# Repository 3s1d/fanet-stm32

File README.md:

# FANET
Flying Ad-hoc Network 

# IDE
Use SW4SRTM32

# Protocol
[Brief specification](https://github.com/3s1d/fanet-stm32/blob/master/Src/fanet/radio/protocol.txt)

# Documentation
[Module (PDF)](https://github.com/3s1d/fanet-stm32/raw/master/fanet_module.pdf)

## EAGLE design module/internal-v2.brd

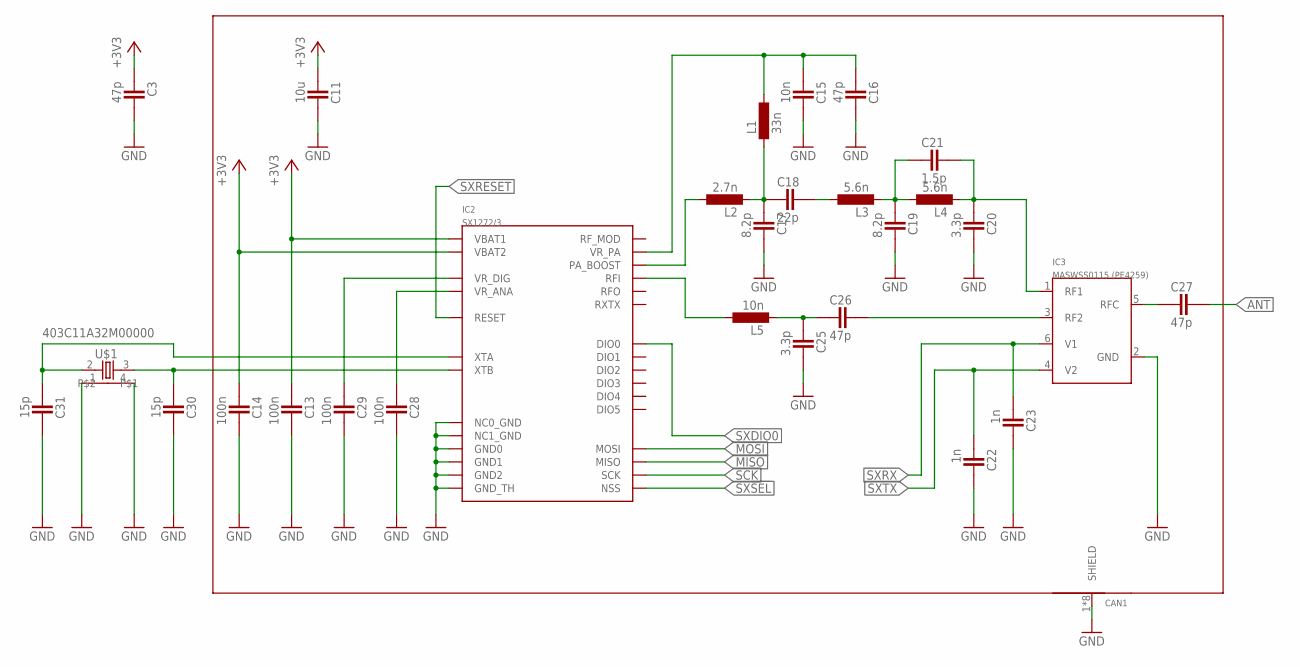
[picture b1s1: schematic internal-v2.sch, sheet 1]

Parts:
C3, C16, C26, C27: 47p; CAPC1005X60N
C11: 10u; CAPC2012X145AN
C13, C14, C28, C29: 100n; CAPC1005X60N
C15: 10n; CAPC1005X60N
C17, C19: 8.2p; CAPC1005X60N
C18: 22p; CAPC1005X60N
C20, C25: 3.3p; CAPC1005X60N
C21: 1.5p; CAPC1005X60N
C22, C23: 1n; CAPC1005X60N
C30, C31: 15p; CAPC1005X60N
CAN1: RF-SHIELD; RF-SHIELDING-13.66X12.70
IC2: SX1272/3; QFN28
IC3: MASWSS0115 (PE4259); SC-70
L1: 33n; INDC1005X60N
L2: 2.7n; INDC1005X60N
L3, L4: 5.6n; INDC1005X60N
L5: 10n; INDC1005X60N
U$1: 403C11A32M00000; MT

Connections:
+3V3: C3.1, C11.1, C13.1, C14.1, IC2.P$1 (VBAT1), IC2.P$15 (VBAT2); also elsewhere on the board
ANT: C27.2
GND: C3.2, C11.2, C13.2, C14.2, C15.2, C16.2, C17.2, C19.2, C20.2, C22.2, C23.2, C25.2, C28.2, C29.2, C30.2, C31.2, CAN1.1, CAN1.2, CAN1.3, CAN1.4, CAN1.5, CAN1.6, CAN1.7, CAN1.8, IC2.P$7 (NC0_GND), IC2.P$8 (NC1_GND), IC2.P$16 (GND0), IC2.P$22 (GND1), IC2.P$26 (GND2), IC2.P$29 (GND_TH), IC3.2 (GND), U$1.1, U$1.4; also elsewhere on the board
MISO: IC2.P$18 (MISO); also elsewhere on the board
MOSI: IC2.P$19 (MOSI); also elsewhere on the board
unnamed: IC2.P$27 (PA_BOOST), L2.2
unnamed: C17.1, C18.1, L1.1, L2.1
unnamed: C15.1, C16.1, IC2.P$28 (VR_PA), L1.2
unnamed: C18.2, L3.2
unnamed: C19.1, C21.1, L3.1, L4.2
unnamed: C27.1, IC3.5 (RFC)
unnamed: C20.1, C21.2, IC3.1 (RF1), L4.1
unnamed: IC2.P$25 (RFI), L5.2
unnamed: C25.1, C26.1, L5.1
unnamed: C26.2, IC3.3 (RF2)
unnamed: C28.1, IC2.P$2 (VR_ANA)
unnamed: C29.1, IC2.P$3 (VR_DIG)
unnamed: C30.1, IC2.P$5 (XTB), U$1.3 (2)
unnamed: C31.1, IC2.P$4 (XTA), U$1.2 (1)
SCK: IC2.P$17 (SCK); also elsewhere on the board
SX!SEL: IC2.P$20 (NSS); also elsewhere on the board
SXDIO0: IC2.P$9 (DIO0); also elsewhere on the board
SXRESET: IC2.P$6 (RESET); also elsewhere on the board
SXRX: C23.1, IC3.6 (V1); also elsewhere on the board
SXTX: C22.1, IC3.4 (V2); also elsewhere on the board

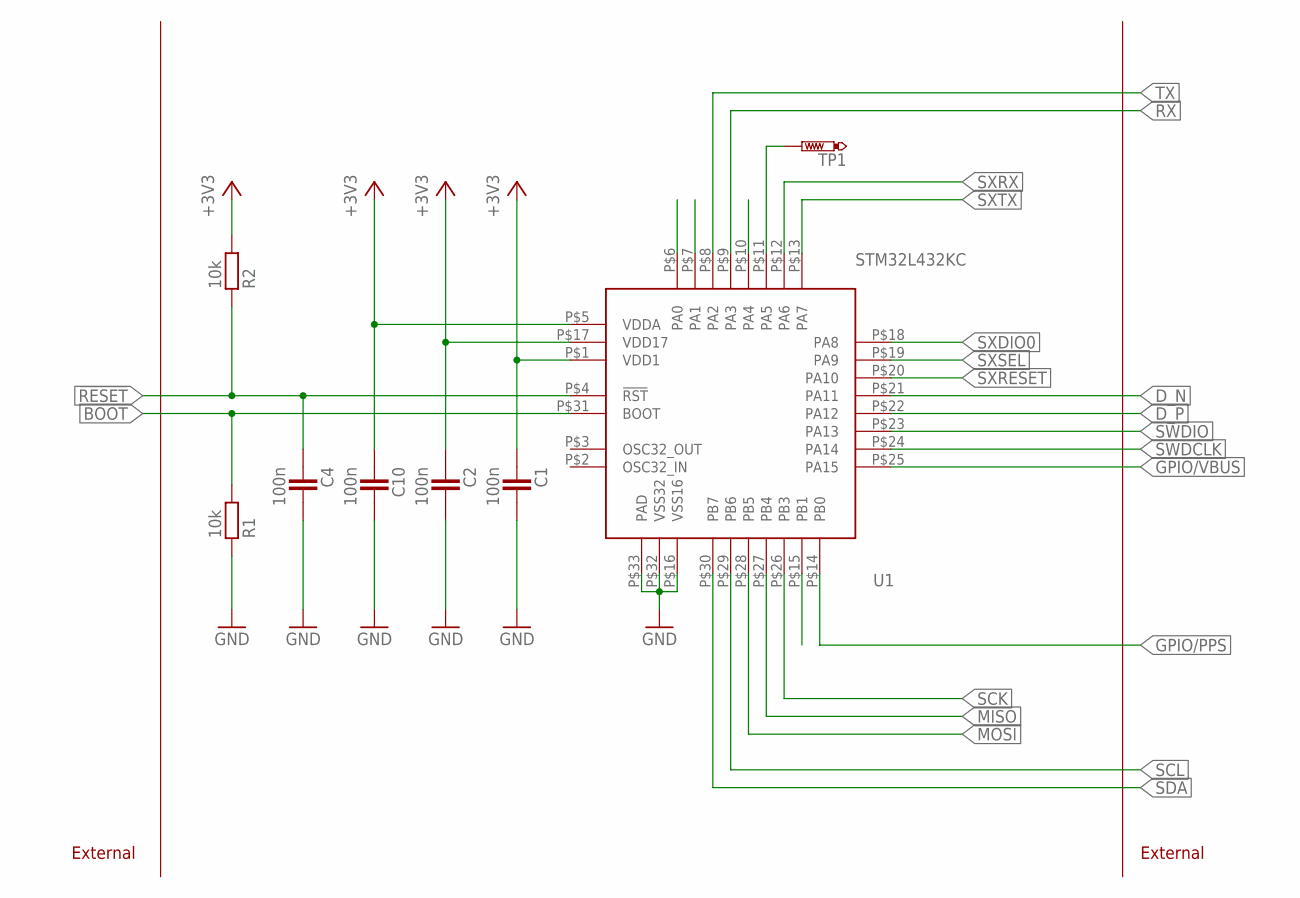
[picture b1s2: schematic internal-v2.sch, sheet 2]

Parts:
C1, C2, C4, C10: 100n; CAPC1005X60N
R1, R2: 10k; RESC1005X40AN
TP1: PTR1TP06R; TP06R
U1: STM32L432KC

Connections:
!RESET: C4.1, R2.1, U1.P$4 (!RST)
+3V3: C1.1, C2.1, C10.1, R2.2, U1.P$1 (VDD1), U1.P$5 (VDDA), U1.P$17 (VDD17); also elsewhere on the board
A0: U1.P$10 (PA4)
A1: TP1.TP, U1.P$11 (PA5)
A2: U1.P$6 (PA0)
A4: U1.P$15 (PB1)
BOOT: R1.2, U1.P$31 (BOOT)
D13: U1.P$7 (PA1)
D_N: U1.P$21 (PA11)
D_P: U1.P$22 (PA12)
GND: C1.2, C2.2, C4.2, C10.2, R1.1, U1.P$16 (VSS16), U1.P$32 (VSS32), U1.P$33 (PAD); also elsewhere on the board
GPIO/PPS: U1.P$14 (PB0)
GPIO/VBUS: U1.P$25 (PA15)
MISO: U1.P$27 (PB4); also elsewhere on the board
MOSI: U1.P$28 (PB5); also elsewhere on the board
RX: U1.P$9 (PA3)
SCK: U1.P$26 (PB3); also elsewhere on the board
SCL: U1.P$29 (PB6)
SDA: U1.P$30 (PB7)
SWDCLK: U1.P$24 (PA14)
SWDIO: U1.P$23 (PA13)
SX!SEL: U1.P$19 (PA9); also elsewhere on the board
SXDIO0: U1.P$18 (PA8); also elsewhere on the board
SXRESET: U1.P$20 (PA10); also elsewhere on the board
SXRX: U1.P$12 (PA6); also elsewhere on the board
SXTX: U1.P$13 (PA7); also elsewhere on the board
TX: U1.P$8 (PA2)

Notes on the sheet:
External

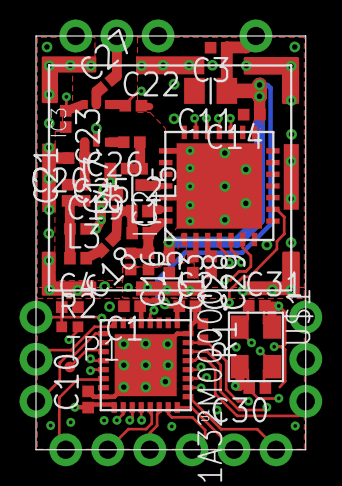
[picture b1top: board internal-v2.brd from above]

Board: 4 copper layers, 15.0 x 23.0 mm, 37 parts (0 on the bottom side), 27 nets.

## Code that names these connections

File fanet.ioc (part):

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Mcu.UserName=STM32L432KCUx
PA9.GPIOParameters=GPIO_Label
PA2.GPIO_Speed=GPIO_SPEED_FREQ_VERY_HIGH
PA3.GPIOParameters=GPIO_Speed
PB0.GPIO_Label=GPIO_PPS_EXTI0
PA6.GPIO_Label=SXRX
PB4\ (NJTRST).GPIO_Speed=GPIO_SPEED_FREQ_VERY_HIGH
PA3.GPIO_Speed=GPIO_SPEED_FREQ_VERY_HIGH
PA2.GPIOParameters=GPIO_Speed
RCC.SYSCLKSource=RCC_SYSCLKSOURCE_PLLCLK
PB3\ (JTDO-TRACESWO).Signal=SPI3_SCK
PB5.GPIOParameters=GPIO_Speed
PA14\ (JTCK-SWCLK).Signal=SYS_JTCK-SWCLK
PA8.GPIOParameters=GPIO_PuPd,GPIO_Label
RCC.HSE_VALUE=8000000
PB0.GPIOParameters=GPIO_PuPd,GPIO_Label
PB5.Mode=Full_Duplex_Master
PA10.GPIO_Label=SXRESET
PA8.Signal=GPXTI8
Mcu.Package=UFQFPN32
PA6.Signal=GPIO_Output
PA10.Signal=GPIO_Output
PA5.GPIOParameters=GPIO_Label
PB5.GPIO_Speed=GPIO_SPEED_FREQ_VERY_HIGH
PA13\ (JTMS-SWDIO).Signal=SYS_JTMS-SWDIO
PA3.Signal=LPUART1_RX
PA6.GPIOParameters=GPIO_Label
PA14\ (JTCK-SWCLK).Mode=Serial_Wire
PA9.GPIO_Label=SXSEL
PA3.Mode=Asynchronous
PB4\ (NJTRST).GPIOParameters=GPIO_Speed
PA8.GPIO_Label=SXDIO0_EXTI8
PA9.Signal=GPIO_Output
PA5.Signal=GPIO_Output
board=fanet
PB3\ (JTDO-TRACESWO).GPIOParameters=GPIO_Speed
PB3\ (JTDO-TRACESWO).Mode=Full_Duplex_Master
PA10.GPIOParameters=GPIO_Label
PB4\ (NJTRST).Mode=Full_Duplex_Master
Mcu.Name=STM32L432K(B-C)Ux
PA2.Signal=LPUART1_TX
PA13\ (JTMS-SWDIO).Mode=Serial_Wire
RCC.SYSCLKFreq_VALUE=18000000
PB5.Signal=SPI3_MOSI
PA7.GPIO_Label=SXTX
PA5.GPIO_Label=TP1
PA8.GPIO_PuPd=GPIO_PULLDOWN
PA2.Mode=Asynchronous
PB3\ (JTDO-TRACESWO).GPIO_Speed=GPIO_SPEED_FREQ_VERY_HIGH
PB0.Signal=GPXTI0
PA7.GPIOParameters=GPIO_Label
PB0.GPIO_PuPd=GPIO_PULLDOWN
PA7.Signal=GPIO_Output
PB4\ (NJTRST).Signal=SPI3_MISO

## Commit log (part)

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2017-05-21 sx1272 working
2017-05-22 fanet working w/o arduino
2017-05-22 readme added
2017-05-22 bumped start to 0x08010000
2017-05-23 cproject
2017-05-23 changed to IT transmitt
2017-05-23 fixed blocking uart
2017-05-24 cleanup
2017-06-05 proper debug scheme
2017-06-05 large packages (>32bytes payload) could potentially have blocked the hole network by blocking athe transmitter. fixed
2017-06-05 typos
2017-06-05 removed mac debugging
2017-08-16 protcol improved by absolute coordinates
2017-08-30 updated app to support new absolute coordinate system
2017-08-31 somem more FLARM relevant extentions
2017-09-03 FSK support added
2017-09-09 GFSK is working
2017-09-09 changed syncword. added airtime model
2017-09-11 address gets stored in flash
2017-09-12 revisited airtime duty cycle model
2017-09-15 sx_receive protected
2017-09-15 reorganized file structure
2017-09-17 bumped to 1.9.0 and removed unneeded buses like USB and I2C
2017-09-17 adjusted frq source to compensate thermal drift
2017-09-19 serial interface extend by fault hanlding
2017-09-19 typo
2017-09-19 minor rounding issue
2017-09-19 minor protocl adjustments
2017-09-28 protocol extension
2017-09-28 added modul eagle library
2017-10-11 pdf added
2017-10-11 extended README
2017-10-12 protocoll extended
2017-10-13 revised remote config
2017-10-14 remote configuration and signature intorduced
2017-10-15 signature corrected
2017-12-06 Manufacturer ID for SoftRF
2018-01-12 tweaked FSK freq. setting FLARM types during operation
2018-05-06 neg turnrate bugfix
2018-06-08 new type
2018-07-04 minor bugfixes
2018-09-29 FANET 1.1
    -code cleanup
    -ground tracking
    -improved landmark interface
2018-09-29 docu
2018-10-02 added geoid separation for FLARM altitudes
2018-10-19 new manucaturer id
2018-10-28 added manufacturer id
2018-11-15 Add Battery Voltage to Service (Type = 4) payload in Fanet protocol
2018-11-15 added softrf manufacturer
2018-11-15 added state of charge for base statinos
2019-06-10 protocol adjustments (landmarks becoming stable)
2019-06-12 wrong comment
2019-06-14 landmark scheme slightly reworked
2019-06-14 added dev flag
2019-06-15 compressed coordinates sample code
2019-06-15 extended landmark circle api
2019-06-15 enlarged radii for landmarks
2019-06-15 unified landmark data sequence
2019-06-21 3d landmarks altitude adjusted/expanded
2019-06-25 wind dependent landmarks
2019-06-26 landmark no wind option
2019-07-13 update remote config
2019-07-24 geo-based forwarding flag (can be ignored by any none-forwarding instances).
2019-07-30 Forwarding bugfix for ACK'ed frames...
2019-08-16 removed unstable us delay
2019-08-20 bootloader updater added
2019-08-20 removed unused code
2019-08-21 landmarks are stabile
2019-08-21 Fanet 1.2 (landmarks)
2019-09-19 comments orrected
2019-10-18 protocol extentions -3d tracking now supports QNE -hardware info for statistics, network optimization (experimental)
2019-10-18 adapated serial interface docu. code still pending
2019-10-19 improved description
2019-10-29 HW info pull'able
2020-02-14 fanet protocol extension
2020-03-16 DF Manufacturer ID
    For DF FANET base and weather station
2020-03-16 added ogn reserved area
2020-03-20 more stabile serial interface
2020-03-21 serial dma circular buffer fix, casw schedluing
2020-05-20 type 1 optinal byes added
2020-05-20 ogn tracker manu id
2020-05-20 changed ogn ID
2020-05-25 -type 1 extrended to fit OGN, Naviter requirements -thermal defined stabile -hw info new defined. experimantal
2020-06-26 introduced manufacturer subsections.
2020-08-03 added flarm addr issue error msg
2020-12-20 GXAircom manufacturer ID
2021-02-28 Airtribune manufacturer ID
2021-04-14 new fanet manufacturer
2021-04-26 new manufacturer ID
2021-05-06 Typos
    Just some typos I've seen while reading through the document.
2021-09-09 added hardware ids
2021-09-09 added note
2021-09-15 tx/rx switch for fsk
2021-10-11 added naviter blade
2021-10-13 added flarm ID
2021-10-18 changed flarm id
2022-01-13 sx1272 driver state fixes
2022-01-14 XC Tracer Manufacturer Range
2022-05-31 sx1262 syncword
2022-07-08 fanet zone 2: 920.8Mhz, docu only
2022-07-08 style
2022-08-08 world wide frequencies. work in progress
2022-12-06 fanet zones + sx reset
2022-12-06 moinor fixes
2022-12-07 reset vector fix
2022-12-11 sx1272 crc issue fixed
2023-08-28 Adds Cloudbuddy manufacturer IDs
    Adds manufacturer for Cloudbuddy gateways as well as Cloudbuddy wind sensors
2023-08-28 Change to one manufacturer ID
    As suggested by Juergen. Thanks!
2023-09-05 tidied up list of manufacturer IDs
2024-01-26 added syscals for latest toolchain
2024-04-21 new device id
2024-07-29 Update protocol.txt - add new manufacturer ID for BlyBeeper devices
2024-11-15 supressed new compilier warning for 1.16.1
2025-02-25 added new manufacturer ID.
2025-03-06 added GeoJSON file of zones.
2025-08-18 new manu
2025-12-01 layout added
